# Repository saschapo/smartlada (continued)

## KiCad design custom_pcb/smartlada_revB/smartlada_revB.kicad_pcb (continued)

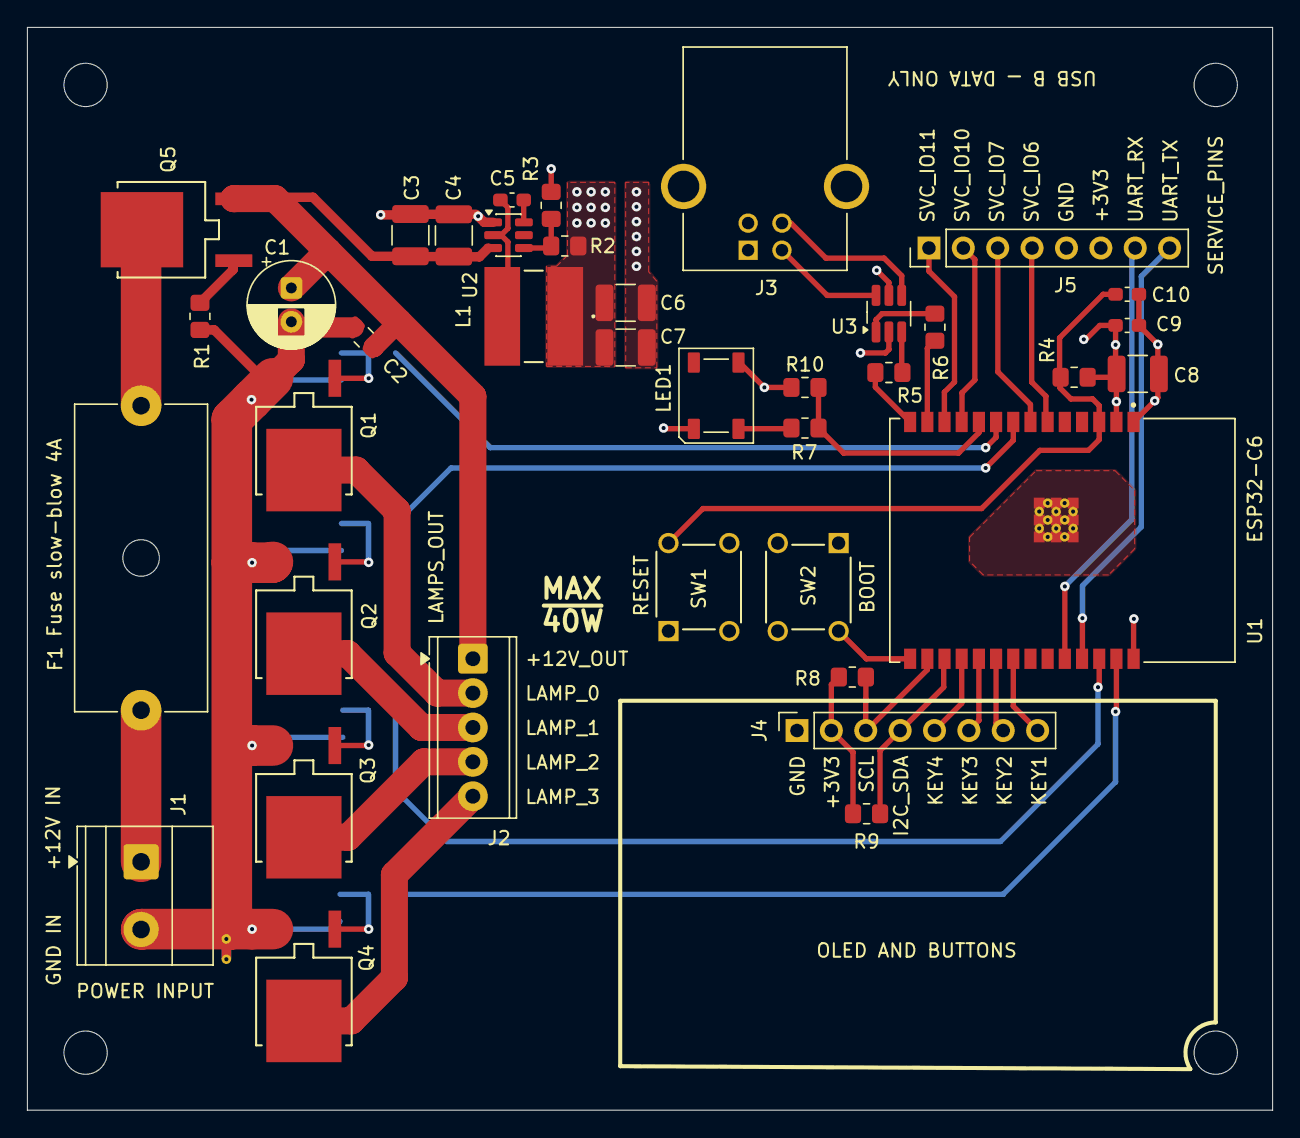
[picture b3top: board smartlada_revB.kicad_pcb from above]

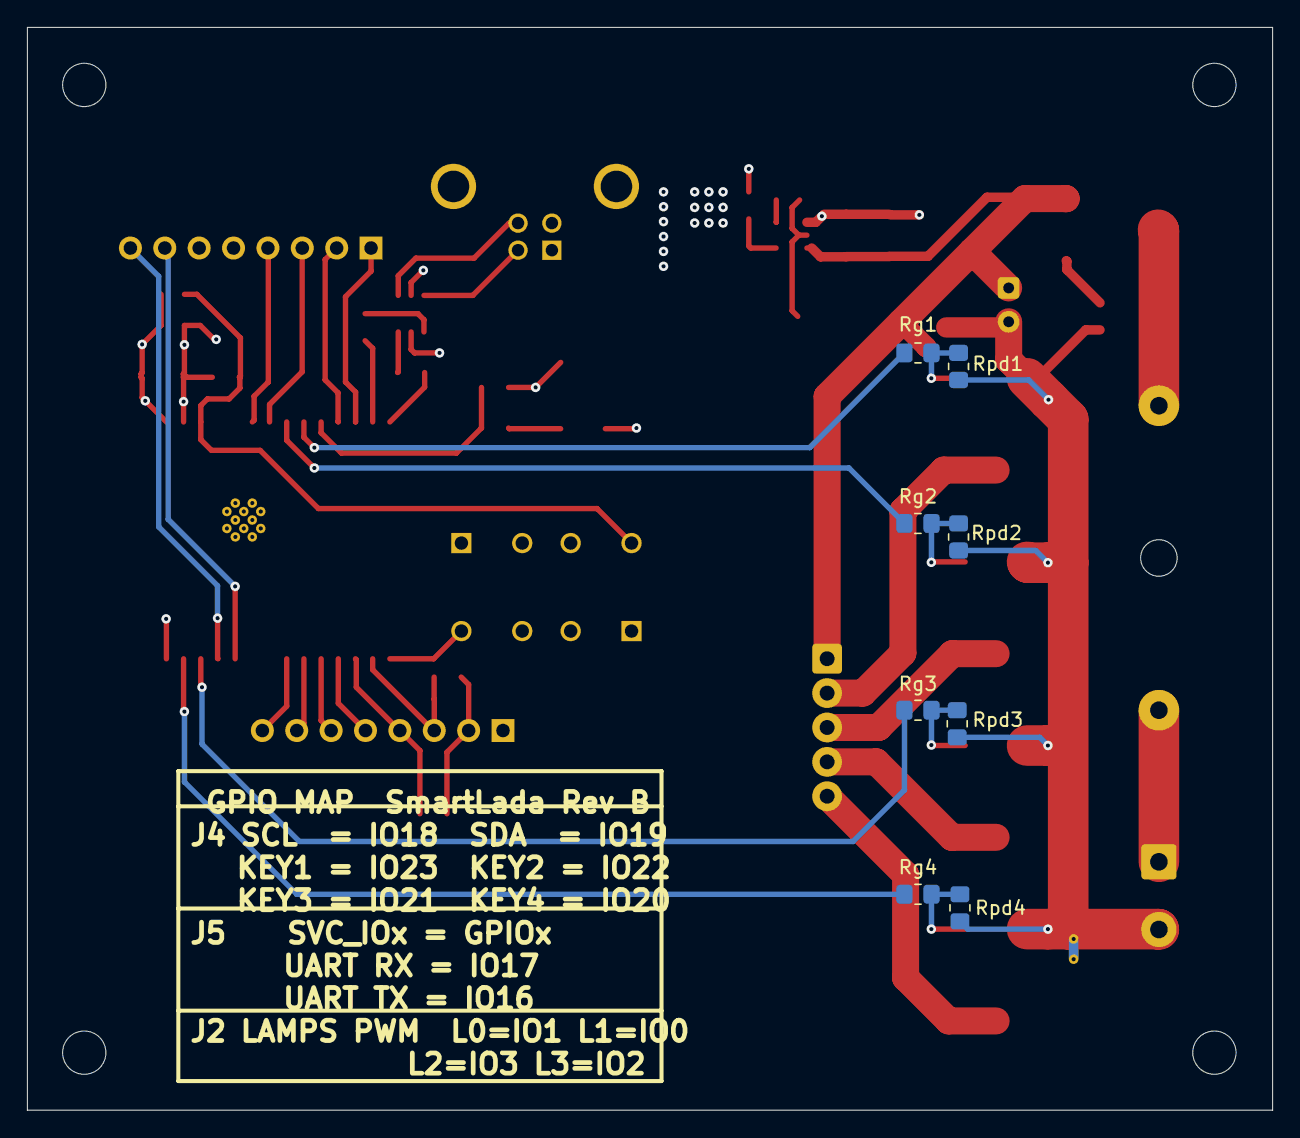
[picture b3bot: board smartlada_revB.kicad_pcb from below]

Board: 4 copper layers, 92.0 x 80.0 mm, 51 parts (8 on the bottom side), 44 nets.

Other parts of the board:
M3_1, M3_2, M3_3, M3_4: MountingHole_3.2mm_M3

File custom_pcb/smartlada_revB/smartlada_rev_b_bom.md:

# SmartLada Rev B — BOM (на 4 платы + запас)

Снято с разведённой платы (2026-07-25). Наличие/цены — Platan (shop.platan.ru), retail.
Модуль U1 — **AliExpress** (не Platan). NT1 — net-tie, физической детали нет.
Правило Platan: для позиций **со склада** (QUANTY>0) продают от 1 шт, MINZAKAZ в API — оптовый.

Поля для KiCad Symbol Fields Table: **MPN** (part number) и **MF** (manufacturer).

## Резисторы 0805 (после унификации номиналов)

| Value | Ref | /плата | Заказ | MPN | MF | Platan NOM | Мин |
|-------|-----|-------|-------|-----|----|-----------|-----|
| 100k | R1,R2,Rpd1..4 | 6 | 30 | ERJP06F1003V | Panasonic | 2015140622 | от 1 |
| 100R | Rg1..4,R7 | 5 | 25 | RT0805BRD07100RL | Yageo | 2014970291 | от 1 |
| 10k | R4,R10,R8,R9 | 4 | 20 | ERJ6ENF1002V | Panasonic | **2014975487** | MIN 1 ✓ |
| 22k | R3 | 1 | 6 | RC0805JR-0722KL | Yageo | **2014967651** | MIN 1 ✓ |
| 0R | R5,R6 | 2 | 10 | (см. ниже) | — | — | ⚠ на Platan только катушка |

**10k/22k — решены** (нашлись MIN-1 order-in линии: Panasonic ERJ6EN 10k, Yageo RC0805JR 22k).
**0R (R5/R6):** MIN-1 линии на Platan нет. Но R5/R6 — это **0 Ω rework-перемычки** в USB-паре
(нативный USB C6 работает при прямом соединении, series-R не нужен — datasheet/§6). Поэтому:
→ **просто запаять пятачки перемычкой/каплей** (детали не нужно), либо взять 0805 0Ω из
AliExpress-набора. Покупать катушку 0R на Platan не обязательно.

## Конденсаторы

| Value | Ref | /плата | Заказ | MPN | MF | Platan NOM | Мин |
|-------|-----|-------|-------|-----|----|-----------|-----|
| 100nF 0603 | C2,C5,C9 | 3 | 15 | TCC0603X7R104K250CT | CCTC | 2017412118 | склад, от 1 |
| 1µF 0603 25V | C10 | 1 | 6 | TCC0603X7R105K250CT | CCTC | 2015754477 | от 1 |
| 10µF 1210 50V | C3,C4 | 2 | 10 | GRM32ER71H106KA12L | Murata | 2014974863 | order-in 1-2д, MIN 1 |
| 22µF 1210 25V | C6,C7,C8 | 3 | 15 | GRT21BR61E226ME13L | Murata | 2015901729 | склад, от 1 |
| 100µF элко 25V | C1 | 1 | 5 | EEUFR1E101 | Panasonic | 2014982023 | от 1 |

*C2 стоит на 0805-футпринте, но 0603-корпус паяется (как в revA) — плату не трогаем.*

## Активные / индуктивность

| Part | Ref | /плата | Заказ | MPN | MF | Platan NOM | Мин |
|------|-----|-------|-------|-----|----|-----------|-----|
| N-MOSFET | Q1..Q4 | 4 | 16 | AOD4184A | A&O | 2010030452 | ⚠ MIN 13 |
| P-MOSFET | Q5 | 1 | 5 | AOD4185 | YouTai | 2017289798 | от 1 |
| Buck | U2 | 1 | 5 | TPS54202DDCR | TI | **2015708243** | от 1 |
| USB ESD | U3 | 1 | 5 | USBLC6-2SC6 | YouTai | 2015469303 | от 1 (8₽) |
| Дроссель 10µH | L1 | 1 | 5 | CDRH6D28NP-100NC | Sumida | 2014962957 | от 1 |
| RGB 5050 | LED1 | 1 | 6 | WS2812B-V5 | WorldSemi | 2016855366 | склад, от 1 |
| Модуль | U1 | 1 | 6 | ESP32-C6-WROOM-1-N16 | Espressif | **AliExpress** | long-lead |

## Разъёмы / механика

| Part | Ref | /плата | Заказ | MPN | MF | Platan NOM | Мин |
|------|-----|-------|-------|-----|----|-----------|-----|
| Клемма 2P 5.0мм | J1 | 1 | 10 | DG127-5.0-02P | Degson | 2013048522 | ⚠ MIN 10 (заказ 5д) |
| ^ альтернатива J1 | J1 | — | — | XY128V-A-2P-5.0 | NXU | 828149532 | ⚠ склад ТОЛЬКО 3 шт (мало на 4 платы) |
| Клемма 5P 2.54мм | J2 | 1 | 5 | DG308-2.54-05P | Degson | 2017108400 | от 1 |
| USB-B розетка | J3 | 1 | 5 | USBB-1J-W | NXU | 249636968 | склад |
| Гнездо 8P female (2.54) | J4 | 1 | 1×PBS-40 (резать) | PBS-40 (DS1023-1x40S21) | Connfly | 2016827819 | склад 333, от 1 |
| Гребёнка 8P male (2.54) | J5 | 1 | 1×PLS-40 (резать) | PLS-40 | KLS | 613861066 | склад 14377, от 1 |
| Кнопка тактовая 6×6 THT | SW1,SW2 | 2 | 10 | 1-1825910-0 (TE, h=7мм — низкая) | TE | 2014974669 | order-in 1-2д, MIN 1 |
| Держатель фьюза 5×20 | F1 | 1 | 5 | S1052-1 | Ruichi | 2017222701 | от 1 |
| Фьюз 4A slow 5×20 | F1 | 1 | 6 | FS-52GT-4.0/250 | Conquer | 2017285955 | от 1 |

## Наличие Platan (снято 2026-07-29, retail)

**Со склада (от 1 шт):** 100nF TCC0603 (850), 22µF GRT21 (10907), WS2812B-V5 (1551),
USB-B USBB-1J-W (5267), PLS-40/J5 (14377), J4 гнездо DS1023-1x40S21 (333).

**Под заказ 1-2 раб.дня, MIN 1** (не склад, но берут от 1): 100k, 100R, 10k, 22k, 1µF,
10µF Murata (замена!), 100µF, AOD4185, TPS54202, USBLC6, дроссель L1, DG308/J2, держатель
фьюза, кнопки 1-1825910-0.

**Требуют внимания (большой MIN или долгий лид):**
- **Q1-4 AOD4184A** — 0 склад, **MIN 13**, 3-4 дня → берём 16.
- **J1 DG127** — 0 склад, **MIN 10**, 5 дней → берём 10.
- **Фьюз FS-52GT-4.0/250** — 0 склад, **лид 1-2 НЕДЕЛИ**, MIN 2 → заказать РАНЬШЕ остального.
- **10µF Hongda HLC1210 (старый) был MIN 1000** → заменён на Murata GRM32ER71H106KA12L (MIN 1).
- **10k/22k/0R** — решены ранее (10k/22k MIN 1; 0R R5/R6 = перемычка, не покупаем).

## Не Platan
- **U1 ESP32-C6-WROOM-1-N16** — AliExpress, **ЗАКАЗАНО 5 шт** (3 шт до 8 авг 2026, 2 шт до 15 авг 2026).
  Взят N16 (16 MB), не N8 — текущая сборка под 16MB/N16 (README) корректна, отдельный 8MB-профиль НЕ нужен.

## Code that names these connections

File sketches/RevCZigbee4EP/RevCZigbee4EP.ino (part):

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
// ---------------- channel hardware map (Rev C routing) ------------------
// Index i == logical channel i == physical Faston OUTi. Rev C netlist:
// OUT0=GPIO1, OUT1=GPIO0, OUT2=GPIO2, OUT3=GPIO3 (low-side D4184, active-HIGH gate).
static const uint8_t NUM_CH = 4;
static const uint8_t CH_PINS[NUM_CH] = {1, 0, 2, 3};   // OUT0..OUT3
// Endpoint id per channel. Suggested lamp meaning (assigned by wiring + app naming):
//   EP10 -> turn signal, EP11 -> brake, EP12 -> marker, EP13 -> reverse.
static const uint8_t EP_ID[NUM_CH] = {10, 11, 12, 13};
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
